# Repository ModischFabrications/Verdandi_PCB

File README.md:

# Verdandi_PCB
KiCad PCB for https://github.com/ModischFabrications/Verdandi

Links can be found at https://github.com/ModischFabrications/Verdandi.

## Retrospective

The no-name I2C level shifter is both too big and the wrong specification for WS2812B LEDs, so feel free to replace it with something more fitting.

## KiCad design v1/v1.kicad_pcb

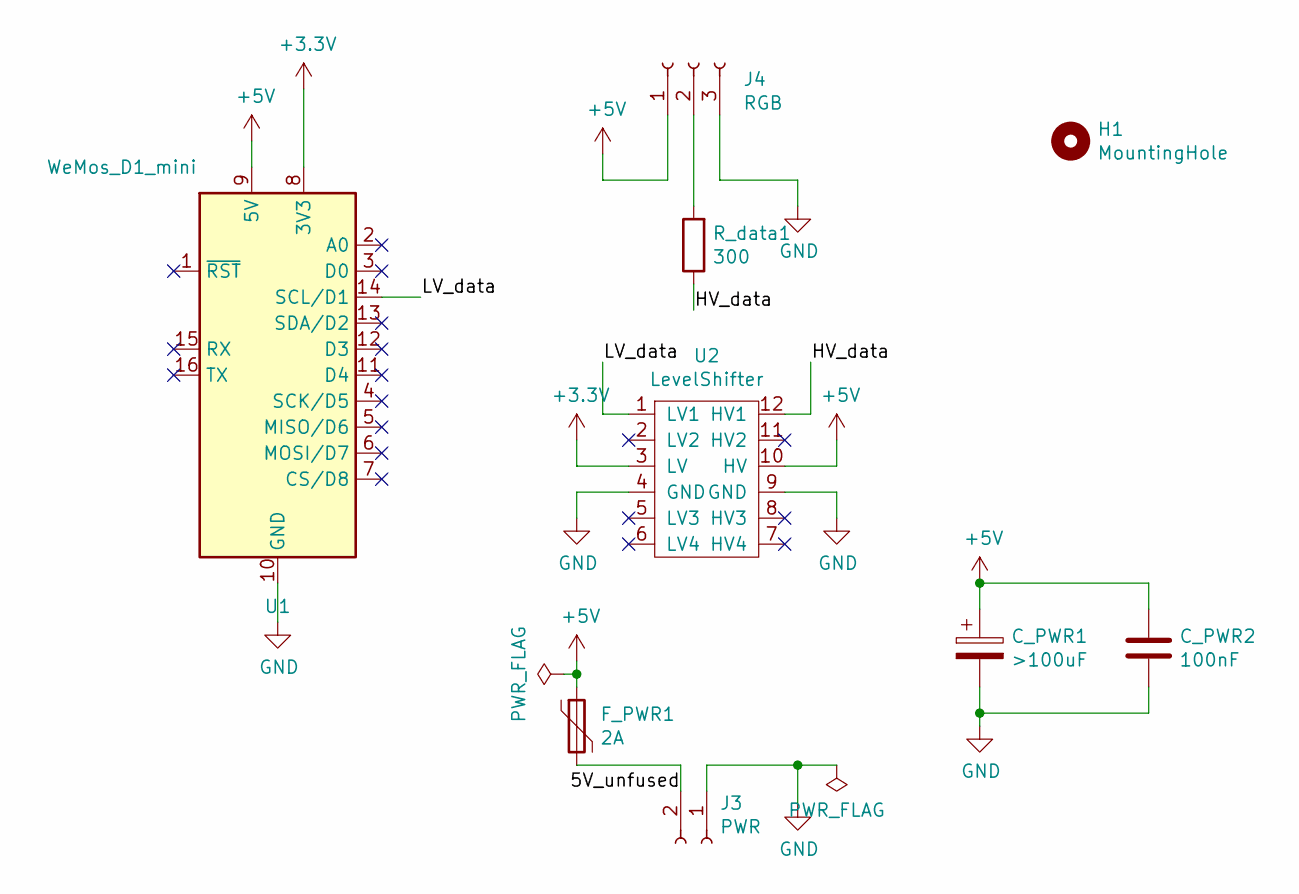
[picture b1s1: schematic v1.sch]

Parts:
C_PWR1: >100uF; CP_Radial_D10.0mm_P5.00mm
C_PWR2: 100nF; C_0603_1608Metric
F_PWR1: 2A; Fuse_1206_3216Metric
H1: MountingHole; MountingHole_3.2mm_M3_DIN965
J3: PWR; JST_XH_S2B-XH-A_1x02_P2.50mm_Horizontal
J4: RGB; JST_XH_S3B-XH-A_1x03_P2.50mm_Horizontal
R_data1: 300; R_0603_1608Metric
U1: WeMos_D1_mini; WEMOS_D1_mini_light
U2: LevelShifter

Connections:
+3V3: U1.8 (3V3), U2.3 (LV)
+5V: C_PWR1.1, C_PWR2.1, F_PWR1.1, J4.1, U1.9 (5V), U2.10 (HV)
/5V_unfused: F_PWR1.2, J3.2
/HV_data: R_data1.1, U2.12 (HV1)
/LV_data: U1.14 (SCL/D1), U2.1 (LV1)
GND: C_PWR1.2, C_PWR2.2, J3.1, J4.3, U1.10 (GND), U2.4 (GND), U2.9 (GND)
unnamed: J4.2, R_data1.2

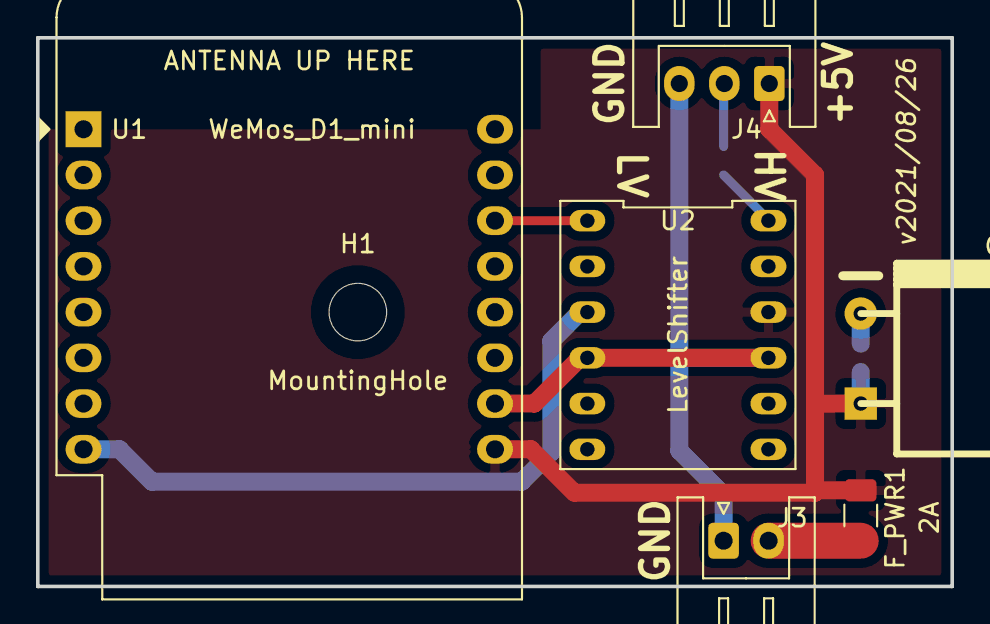
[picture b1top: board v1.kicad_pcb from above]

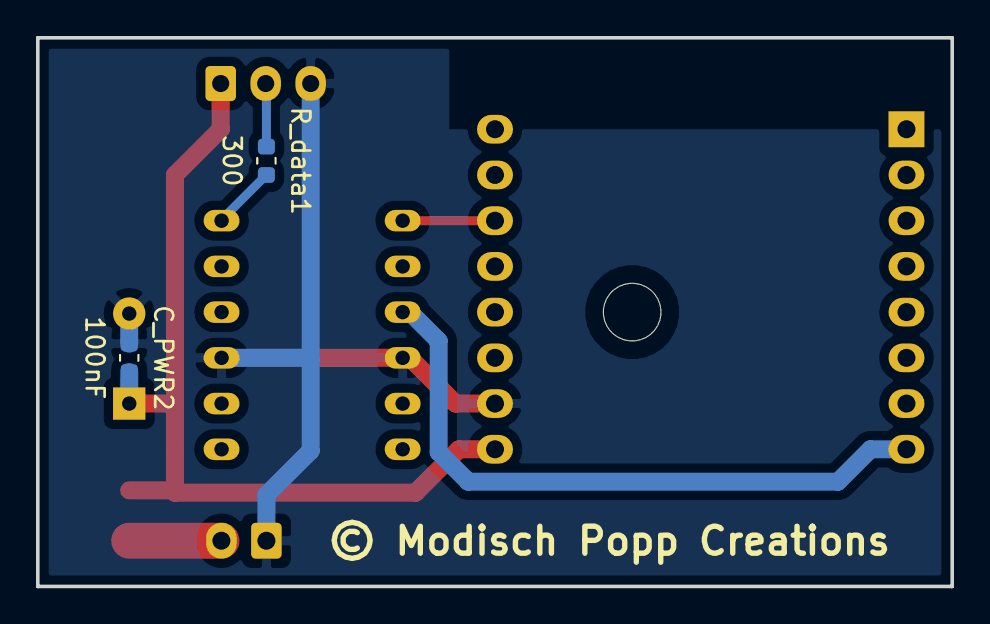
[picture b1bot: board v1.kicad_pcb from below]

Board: 2 copper layers, 50.8 x 30.5 mm, 9 parts (2 on the bottom side), 7 nets.

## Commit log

2020-01-07 add .git*
2020-01-07 init; perfboard ready, PCB missing logo
2020-01-07 add version number, logo and copyright
2020-01-07 add gerber compiling
2020-01-07 angled capacitor
2020-01-08 refine version number and add logo to top
2020-01-08 cleanup
2020-03-28 Create LICENSE
2021-08-26 add autobuild of PCB images
2021-08-26 ignore cache file
2021-08-26 fix level converter footprint
2021-08-26 refine autobuild
2021-08-26 extend readme, add badge

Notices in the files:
v1/v1.kicad_pcb:
© Modisch Popp Creations
